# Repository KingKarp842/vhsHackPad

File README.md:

# vhsHackPad

This project took me around 30 hours total. It was definitely not a straight line from idea to finished macropad, but that was kind of the point. I wanted to make something more advanced than my previous macropad, and vhsHackPad ended up being a mix of PCB design, CAD, firmware, artwork, and a lot of fixing small problems that turned into bigger problems.

## Project Desc.
vhsHackPad is a custom macropad I made for VHS Hack Club. It uses a custom RP2040-based PCB, mechanical keyboard switches, USB-C, and a custom 3D printed enclosure. Instead of using a separate development board, I put the RP2040 and all the supporting parts directly onto the PCB, which made the board thinner and feel more like a real finished device.

I also wanted the PCB to be part of the design instead of something hidden inside the case. The board has custom silkscreen artwork and branding like "vhsHackPad," "Designed by Preston Nguyen," and "Made For VHS Hack Club." I also experimented with exposed ENIG/gold artwork so some of the art would show up as shiny gold on the finished PCB.

The enclosure was designed around the PCB and switches, with a slide-in style case instead of a bunch of screws. That part sounded simple at first, but the tolerances and tabs ended up taking multiple versions before they felt reasonable.

## Main Features
- Custom RP2040 PCB
- USB-C
- Mechanical keyboard switches
- Programmable macropad firmware
- Custom PCB artwork/silkscreen
- Exposed ENIG/gold decorative PCB features
- Custom CAD enclosure
- Slide-in enclosure/tabs
- 3D printed on a Bambu Lab P1S
- Designed specifically for VHS Hack Club
- JLCPCB/JLCPCB assembly-compatible PCB design

## Creation Process
1. Initial Idea & Planning
- I started vhsHackPad because I wanted to make a custom macropad specifically for VHS Hack Club. I had already made a macropad before using a XIAO RP2040, so this time I wanted to level it up by putting the RP2040 directly onto my own PCB. I also wanted the board to actually look cool and show the Hack Club/maker side of the project, not just be a plain circuit board hidden under keycaps.

2. Designing the Schematic
- I started the electronics in KiCad. I added the RP2040, USB-C, power circuitry, crystal, switches, and all the smaller supporting components that the RP2040 needs. Since I was not using a dev board this time, I had to actually understand how the chip was wired instead of just plugging into pins on a premade board.

I also added a GPIO pinout for fun because I had enough room and thought it would be cool if the macropad could technically act kind of like a dev board too, even though I would not really recommend using it that way. One of the harder parts here was figuring out the crystal and some of the RP2040 support circuitry. I had to check which crystal pins were the actual signal pins and which ones needed to be grounded. After fixing that and cleaning up a few other schematic issues, I could finally move on to the PCB layout.

3. PCB Layout & Routing
- The PCB layout was probably one of the biggest parts of the whole project. I had to place the switches, USB-C port, RP2040, flash, crystal, power parts, and a bunch of tiny components on a board that I still wanted to keep compact.

At first I kept moving the MCU around because every placement seemed to fix one problem and create another one. If the RP2040 was in one spot, the USB routing was easier but the switch traces were worse. If I moved it somewhere else, the support components fit better but routing got messy again. I probably moved the MCU back and forth way more times than I expected.

This was also my first time working with an embedded MCU directly on a board, so I had to research where the supporting components should go relative to the chip. The crystal and decoupling capacitors could not just be thrown anywhere. I had to think about keeping important parts close while still making room for the switches and artwork.

Routing was dense because there were a lot of parts fighting for space on a small board. I went through DRC multiple times while fixing clearance problems, routing issues, and unconnected pads. Eventually, I got the actual electrical design down to 0 unconnected pads, 0 footprint errors, and 0 electrical clearance violations. The remaining warnings were mostly silkscreen-related instead of real electrical problems.

Figuring out how to route all the parts to the MCU properly

Finished Routing

3D Render

4. Custom PCB Artwork
- I did not want the PCB to just look like a normal circuit board, so I spent a good amount of time adding custom artwork and branding. I added vhsHackPad, Designed by Preston Nguyen, Made For VHS Hack Club, the board version/date, and a bunch of Orpheus art that looked really good on the render.

The exposed copper/ENIG art was also a learning thing. I had to figure out how copper, solder mask openings, and silkscreen all interacted. Some details that looked fine on screen were too tiny to manufacture cleanly, so I had to simplify parts of the artwork and make sure it would still look decent on the real PCB.

Copper flag art

Orpheus (Hack Club Mascot) silk art!

3D Render w/ Silk

5. Preparing the PCB for Manufacturing
- While designing the board, I kept manufacturing and assembly in mind. I checked components and tried to pick parts that would keep the PCB reasonably inexpensive and compatible with economical PCB assembly instead of making the board way more expensive than it needed to be.

I also checked the final PCB for errors before calling it ready. This was important because once the board is manufactured, a small mistake can turn into a much more annoying problem. I made sure the important electrical issues were fixed before moving forward.

Matching Parts

Render of the pcb (obviously in black)

6. Designing the Enclosure
- Once the PCB was mostly finished, I started designing the enclosure. I used measurements from my previous macropad as a starting point because I already had a rough idea of what worked and what did not.

For this version, I made the switch openings around 15.75 mm x 15.75 mm because I did not want the switches to clip in too tightly. I wanted the build to be removable enough that the board could still be accessed. I also had to balance the spacing between the switches and the case edges so it stayed compact without making everything cramped.

7. Fixing Switch & Case Clearances
- Some of the original CAD dimensions looked fine in SolidWorks but were too tight for real 3D printing. That was one of the bigger lessons from the enclosure: if two parts are modeled with basically no tolerance, they are probably not going to slide together nicely after printing.

I had to go back and resize the switch openings, spacing, and walls. The slide-in tabs especially needed adjustments because the first versions were either too tight or just not practical. I went through about 4 versions of the enclosure, changing a measurement, checking what it affected, and then changing nearby features too.

8. Designing the Slide-In Case
- I wanted the enclosure pieces to slide together instead of using a bunch of screws, so I designed small slide-in tabs with matching openings. This ended up being way more annoying than I expected.

Originally, some of the tabs and openings were around 0.60 mm and 0.75 mm, but that was too close for 3D printing. A tab that is the same size as the slot in CAD does not magically fit perfectly in real life. I experimented with smaller tab dimensions, including around 0.45 mm for a 0.60 mm opening, so there would actually be some clearance.

The goal was to make the case tight enough that it would not randomly fall apart, but loose enough that it could still slide together without feeling like I was about to break it. This part took a lot of tiny edits.

Solidworks Crashed alot... also lapse didn't work on all of CAD...

9. Iterating the CAD
- A lot of the CAD process was basically fixing one thing and then realizing that the fix affected something else. Changing the tabs affected the nearby walls. Changing wall thickness affected how much space the PCB had. Changing clearances affected whether the slide-in case felt usable.

For example, when I changed dimensions from around 0.75 mm to 0.60 mm, I also had to adjust distances between those features and the walls. It was not just one magic number that fixed everything. I had to keep checking the whole case as one system.

SolidWorks also crashed a lot, which made the process more frustrating because I could not always just smoothly iterate. Still, after enough versions, the enclosure ended up in a much better place than the first model.

Top View of Finished CAD

FINISHED CAD

10. Final Hardware Design
- After the electronics, PCB layout, artwork, enclosure, and tolerance work, I ended up with a complete vhsHackPad design. This was a big step up from my previous macropad because I was no longer building around a premade RP2040 board. I designed the RP2040 electronics into the PCB myself, which made the final build cleaner and more complete.

The manufactured PCB honestly came out really nice, especially the artwork. The enclosure and acrylic were less perfect. I used score-and-snap for the acrylic, and one of the corners did not snap cleanly along the line. The top-left corner ended up looking kind of ugly because I rushed it and did not support/snap it as carefully as I should have. It still works, but it is definitely a visible reminder that the physical build matters just as much as the CAD.

Manufactured PCB! (IT LOOKS SO GOOD YAYY)

I was scoring and snapping the acrylic and got lazy so the top left is snapped weird

Final Assembled Build

11. Programming the HackPad
- After the hardware was designed, I worked on the firmware that makes the HackPad act like a keyboard. I used CircuitPython with KMK to program the RP2040 and assign actions to the mechanical switches.

This also needed multiple updates instead of working perfectly the first time. I had to make sure the switch pins in the firmware matched the GPIO pins I chose in the PCB design. Since the PCB was custom, the code had to match my actual hardware layout, not some default macropad layout from online.

The firmware is easy to change later, so the keys can be remapped to different shortcuts or functions without changing the hardware. That was one of the reasons I wanted to use KMK/CircuitPython in the first place.

12. Testing & Iterating the Firmware
- Once the firmware was on the board, I tested the switches to make sure each key press was detected and sent the expected keyboard input over USB. Some things needed fixing. One of the main bugs was that the left and right arrow keys were backwards, so pressing the physical left key would act like right, and pressing the right key would act like left.

To fix it, I had to compare the code against the actual PCB pin assignments and key layout, then update the keymap so the physical keys matched what they were supposed to do. I also updated the firmware multiple times while testing different key assignments and making sure the macropad behaved like a normal USB keyboard.

This part reminded me that a PCB can be electrically fine and still need software debugging. The code running is not the same thing as every key doing the correct thing.

Check out the CODE README under the Firmware section!

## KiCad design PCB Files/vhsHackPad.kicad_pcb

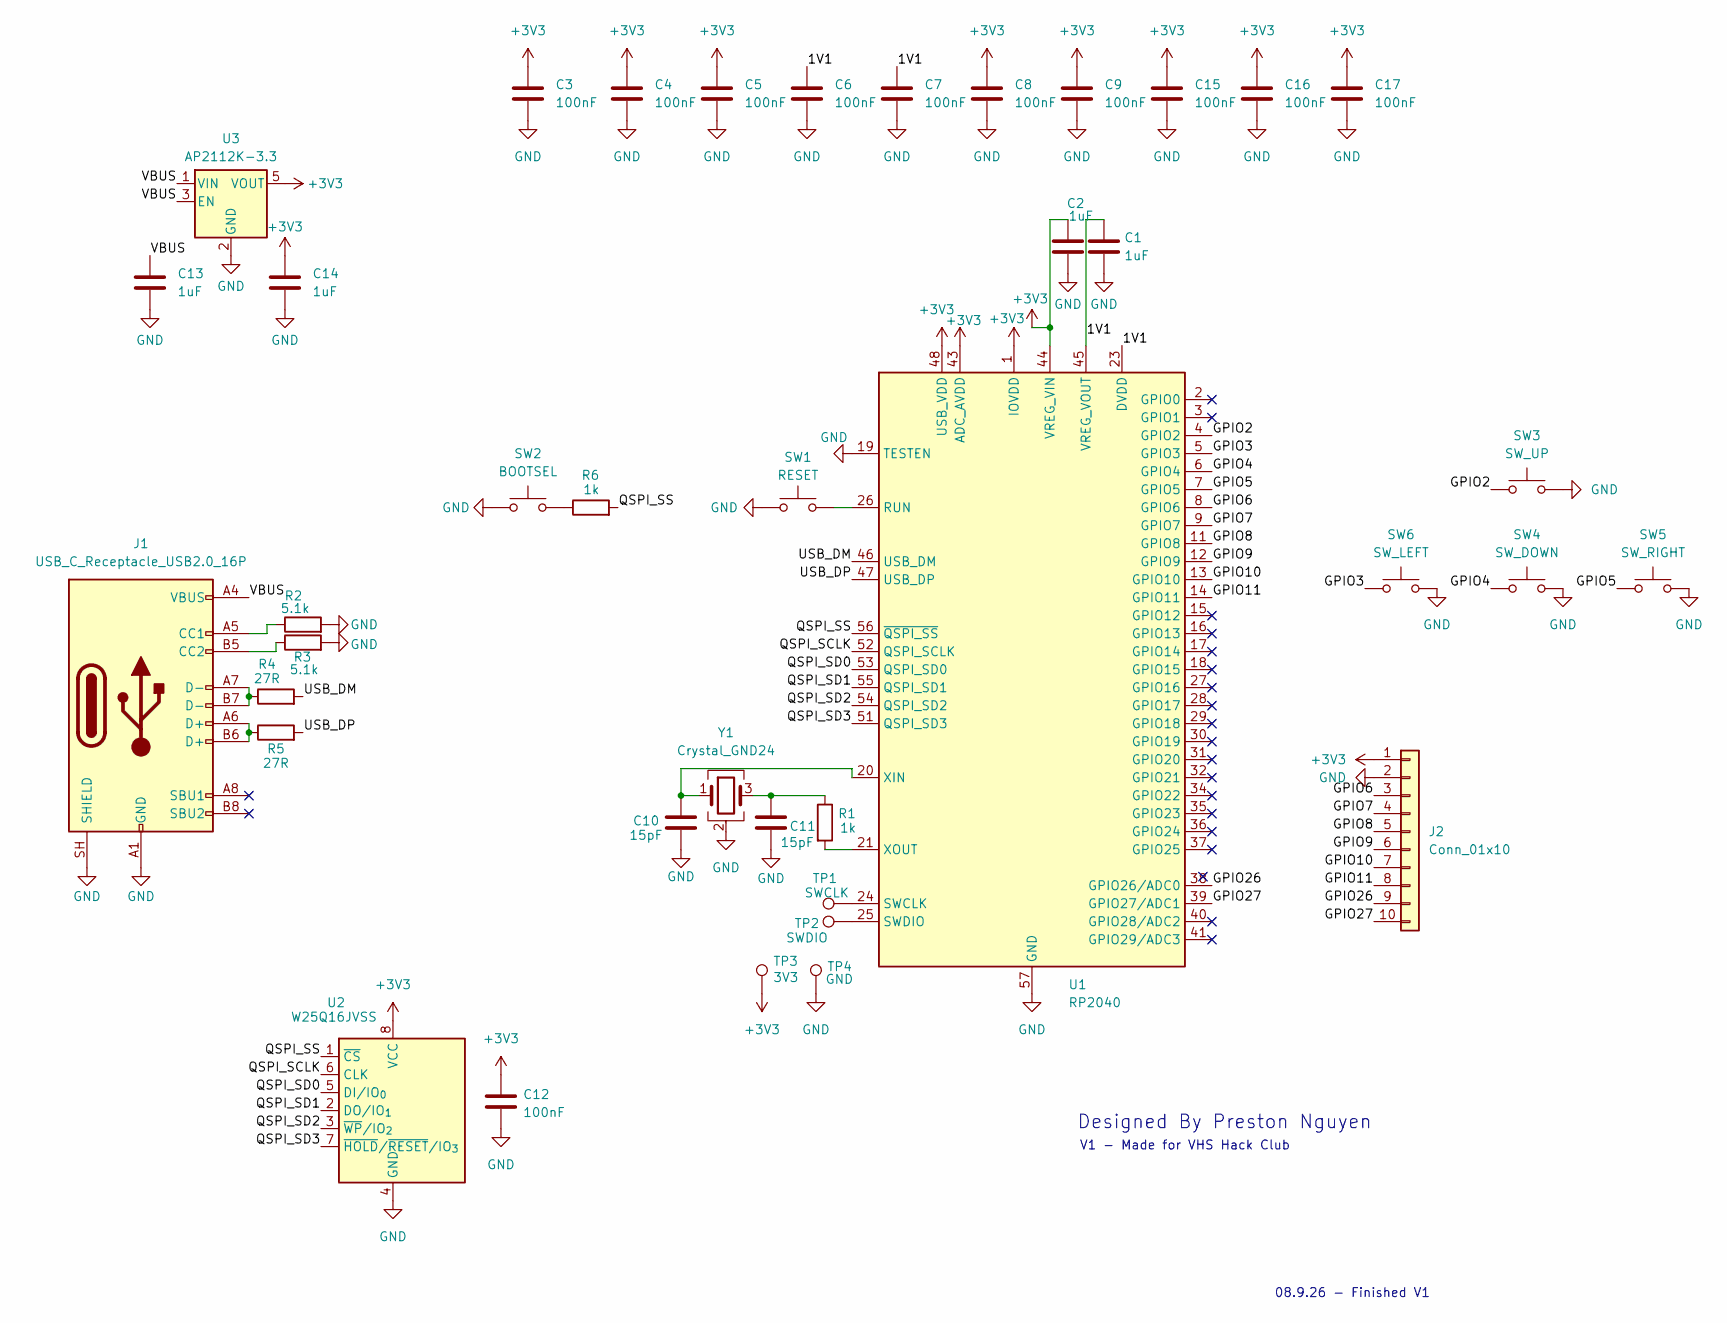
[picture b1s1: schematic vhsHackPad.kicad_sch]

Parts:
C1, C2, C13, C14: 1uF; C_0603_1608Metric
C3, C4, C5, C6, C7, C8, C9, C12, C15, C16, C17: 100nF; C_0603_1608Metric
C10, C11: 15pF; C_0603_1608Metric
J1: USB_C_Receptacle_USB2.0_16P; USB_C_Receptacle_HRO_TYPE-C-31-M-12
J2: Conn_01x10; PinHeader_1x10_P2.54mm_Vertical
R1, R6: 1k; R_0603_1608Metric
R2, R3: 5.1k; R_0603_1608Metric
R4, R5: 27R; R_0603_1608Metric
SW1: RESET; SW_SPST_TL3305A
SW2: BOOTSEL; SW_SPST_TL3305A
SW3: SW_UP; SW_Cherry_MX_1.00u_PCB
SW4: SW_DOWN; SW_Cherry_MX_1.00u_PCB
SW5: SW_RIGHT; SW_Cherry_MX_1.00u_PCB
SW6: SW_LEFT; SW_Cherry_MX_1.00u_PCB
TP1: SWCLK; TestPoint_Pad_D1.5mm
TP2: SWDIO; TestPoint_Pad_D1.5mm
TP3: 3V3; TestPoint_Pad_D1.5mm
TP4: GND; TestPoint_Pad_D1.5mm
U1: RP2040; QFN-56-1EP_7x7mm_P0.4mm_EP3.2x3.2mm
U2: W25Q16JVSS; SOIC-8_5.3x5.3mm_P1.27mm
U3: AP2112K-3.3; SOT-23-5
Y1: Crystal_GND24; Crystal_SMD_3225-4Pin_3.2x2.5mm

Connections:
+3V3: C2.1, C3.1, C4.1, C5.1, C8.1, C9.1, C12.1, C14.1, C15.1, C16.1, C17.1, J2.1, TP3.1 (1_1), U1.1 (IOVDD), U1.10 (IOVDD), U1.22 (IOVDD), U1.33 (IOVDD), U1.42 (IOVDD), U1.43 (ADC_AVDD), U1.44 (VREG_VIN), U1.48 (USB_VDD), U1.49 (IOVDD), U2.8 (VCC), U3.5 (VOUT)
/1V1: C1.1, C6.1, C7.1, U1.23 (DVDD), U1.45 (VREG_VOUT), U1.50 (DVDD)
/GPIO2: SW3.1, U1.4 (GPIO2)
/GPIO3: SW6.1, U1.5 (GPIO3)
/GPIO4: SW4.1, U1.6 (GPIO4)
/GPIO5: SW5.1, U1.7 (GPIO5)
/GPIO6: J2.3, U1.8 (GPIO6)
/GPIO7: J2.4, U1.9 (GPIO7)
/GPIO8: J2.5, U1.11 (GPIO8)
/GPIO9: J2.6, U1.12 (GPIO9)
/GPIO10: J2.7, U1.13 (GPIO10)
/GPIO11: J2.8, U1.14 (GPIO11)
/GPIO26: J2.9, U1.38 (GPIO26/ADC0)
/GPIO27: J2.10, U1.39 (GPIO27/ADC1)
/QSPI_SCLK: U1.52 (QSPI_SCLK), U2.6 (CLK)
/QSPI_SD0: U1.53 (QSPI_SD0), U2.5 (DI/IO_{0})
/QSPI_SD1: U1.55 (QSPI_SD1), U2.2 (DO/IO_{1})
/QSPI_SD2: U1.54 (QSPI_SD2), U2.3 (~WP/IO_{2})
/QSPI_SD3: U1.51 (QSPI_SD3), U2.7 (~HOLD/~RESET/IO_{3})
/QSPI_SS: R6.2, U1.56 (~QSPI_SS), U2.1 (~CS)
/USB_DM: R4.2, U1.46 (USB_DM)
/USB_DP: R5.2, U1.47 (USB_DP)
/VBUS: C13.1, J1.A4 (VBUS), J1.A9 (VBUS), J1.B4 (VBUS), J1.B9 (VBUS), U3.1 (VIN), U3.3 (EN)
GND: C1.2, C2.2, C3.2, C4.2, C5.2, C6.2, C7.2, C8.2, C9.2, C10.2, C11.2, C12.2, C13.2, C14.2, C15.2, C16.2, C17.2, J1.A1 (GND), J1.A12 (GND), J1.B1 (GND), J1.B12 (GND), J1.SH (SHIELD), J2.2, R2.2, R3.2, SW1.1, SW2.1, SW3.2, SW4.2, SW5.2, SW6.2, TP4.1 (1_1), U1.19 (TESTEN), U1.57 (GND), U2.4 (GND), U3.2 (GND), Y1.2 (G), Y1.4 (G)
unnamed: C11.1, R1.1, Y1.3
unnamed: J1.A5 (CC1), R2.1
unnamed: J1.B5 (CC2), R3.1
unnamed: J1.A6 (D+), J1.B6 (D+), R5.1
unnamed: J1.A7 (D-), J1.B7 (D-), R4.1
unnamed: R6.1, SW2.2
unnamed: SW1.2, U1.26 (RUN)
unnamed: TP1.1 (1_1), U1.24 (SWCLK)
unnamed: TP2.1 (1_1), U1.25 (SWDIO)
unnamed: C10.1, U1.20 (XIN), Y1.1
unnamed: R1.2, U1.21 (XOUT)

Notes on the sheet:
08.9.26 - Finished V1
V1 - Made for VHS Hack Club
Designed By Preston Nguyen

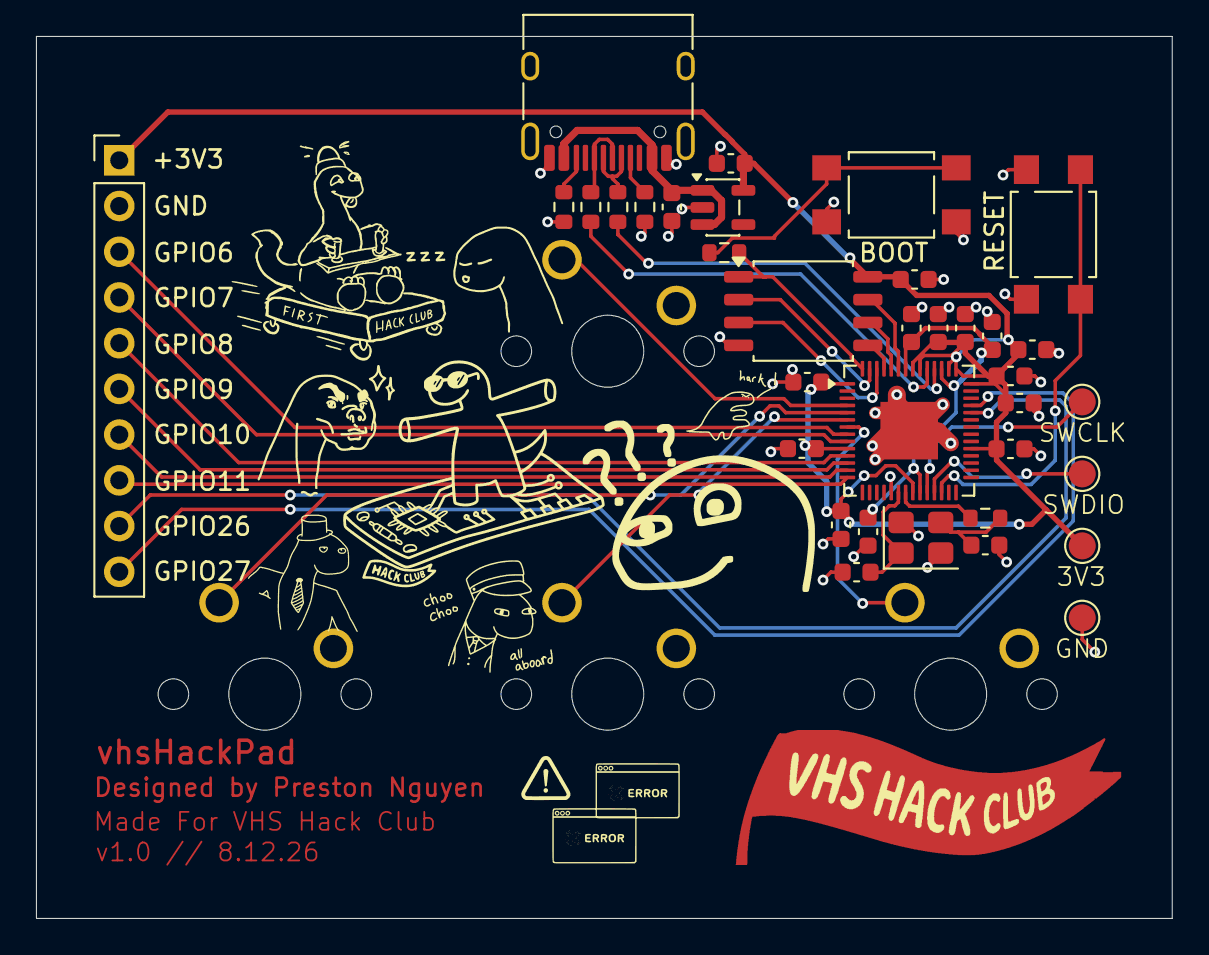
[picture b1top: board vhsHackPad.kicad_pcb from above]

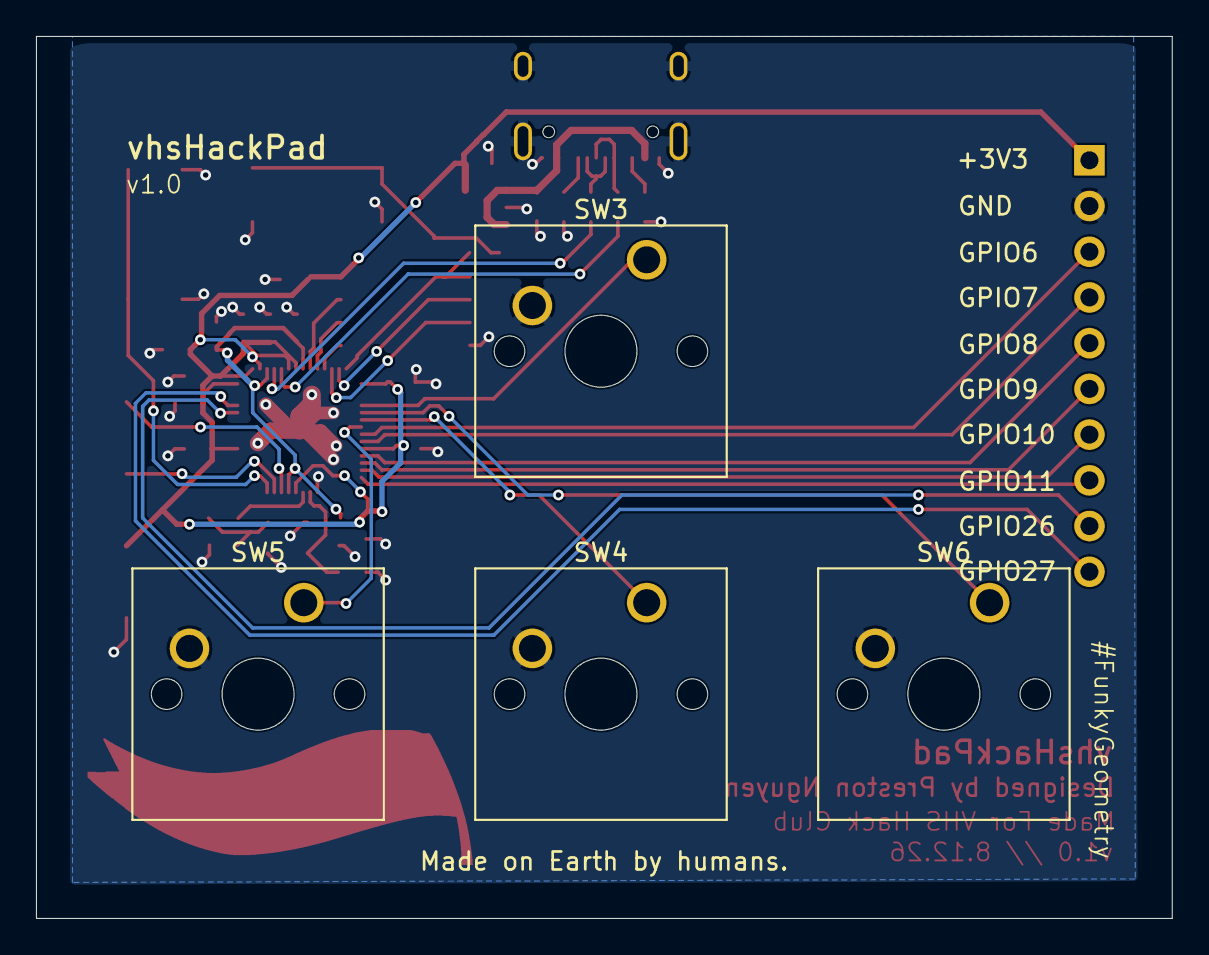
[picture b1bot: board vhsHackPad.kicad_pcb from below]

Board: 2 copper layers, 63.1 x 49.0 mm, 39 parts (4 on the bottom side), 35 nets.
